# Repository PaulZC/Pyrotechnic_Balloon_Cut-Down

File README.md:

# Pyrotechnic Balloon Cut-Down Device

A lightweight wireless cut-down device for use on high altitude balloons.

Designed to be triggered by the [Iridium Beacon Radio Board](https://github.com/PaulZC/Iridium_Beacon_Radio_Board) and equipped with an
[LPRS eRIC4 or eRIC9 integrated radio module](http://www.lprs.co.uk/products/easyradio-ism-modules/eric-soc-rf-modules.html),
the cut-down will be triggered when the eRIC receives its own (unique) serial number on the chosen channel. The number of cut-downs that could be
triggered by a single Iridium Beacon is essentially unlimited.

See [How do I configure the altitude limit](https://github.com/PaulZC/Pyrotechnic_Balloon_Cut-Down/blob/master/LEARN.md#how-do-i-configure-the-altitude-limit)
for details on how to set the altitude limit using the I/O pins or via radio.

The cutter has been designed to reliably sever size 4N (2.4mm) braided nylon cord.

The cut-down device could also be used to control:
- a nichrome hot wire cord cutter
- a strobe or audible alarm
- any other device which can operate from 3.3V to 4.8V (depending on the battery voltage)

See [LEARN.md](https://github.com/PaulZC/Pyrotechnic_Balloon_Cut-Down/blob/master/LEARN.md) for further details.

See [ASSEMBLY.md](https://github.com/PaulZC/Pyrotechnic_Balloon_Cut-Down/blob/master/ASSEMBLY.md) for details on how to assemble and configure the PCB.

See [CUTTER.md](https://github.com/PaulZC/Pyrotechnic_Balloon_Cut-Down/blob/master/CUTTER.md) for details on how to assemble the mechanical parts.

See [Pyro_Cut-Down_V2.pdf](https://github.com/PaulZC/Pyrotechnic_Balloon_Cut-Down/blob/master/Pyro_Cut-Down_V2.pdf) for the schematic,
layout and Bill Of Materials.

The [Eagle](https://github.com/PaulZC/Pyrotechnic_Balloon_Cut-Down/tree/master/Eagle) directory contains the schematic and pcb design files.

The [eRIC](https://github.com/PaulZC/Pyrotechnic_Balloon_Cut-Down/tree/master/eRIC) directory contains the code for the eRIC integrated controller.

The [Drawings](https://github.com/PaulZC/Pyrotechnic_Balloon_Cut-Down/tree/master/Drawings) directory contains the drawings for the mechanical parts.

### Disclaimer

As this project involves the use of a very small quantity of smokeless gunpowder, the information contained herein should only be used by responsible adults
in full compliance with local laws and regulations regarding the purchase, transport, storage and use of smokeless powder. Follow the manufacturer's
instructions and safety information at all times. Appropriate Personal Protective Equipment must be used when handling gunpowder. Keep all parts of this
project out of the reach of children. Proceed entirely at your own risk.

The information contained herein is provided in good faith and is believed by the author to be both accurate and safe, but in no event shall the
author be liable for any injuries or damages resulting from the use of this information howsoever caused.

### Citation

If you have found this project useful and if you are able to, please cite the paper:

P. Clark et al, An open source toolkit for the tracking, termination and recovery of high altitude balloon flights and payloads, 2019 JINST 14 P04003
[DOI:10.1088/1748-0221/14/04/P04003](https://doi.org/10.1088/1748-0221/14/04/P04003)

The Accepted Manuscript is available on arXiv: http://arxiv.org/abs/1904.04321

### License

This project is distributed under a Creative Commons Attribution + Share-alike (BY-SA) licence.
Please refer to section 5 of the licence for the "Disclaimer of Warranties and Limitation of Liability".

Enjoy!

**_Paul_**

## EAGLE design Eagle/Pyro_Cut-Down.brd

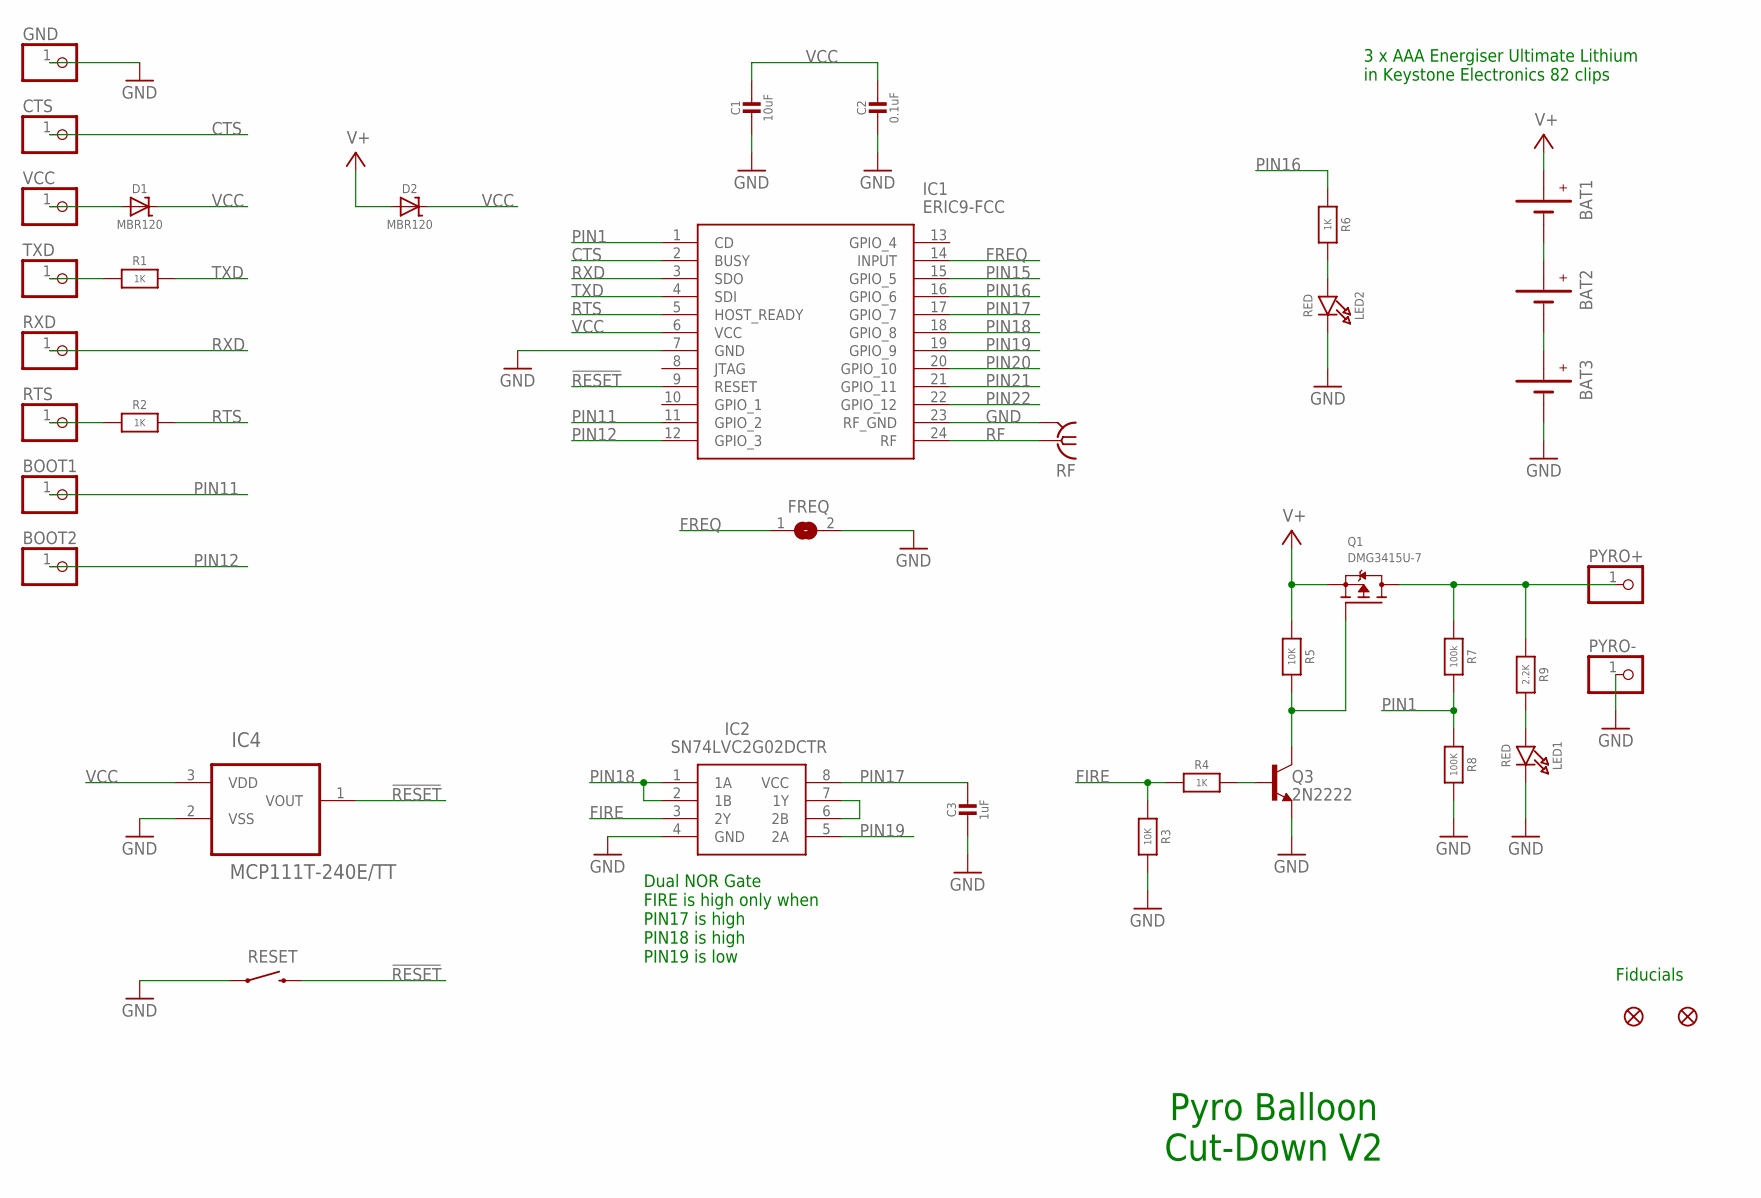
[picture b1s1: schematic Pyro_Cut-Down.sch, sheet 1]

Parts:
BAT1, BAT2, BAT3: BATTERYKEYSTONE82; BATTERY-AAA-KEYSTONE82
BOOT1, BOOT2: PINHD-1X1; 1X01
C1: 10uF; 0805-NO
C2: 0.1uF; 0603-NO
C3: 1uF; 0603-NO
CTS: PINHD-1X1; 1X01
D1, D2: MBR120; SOD-123
FD1, FD2: FIDUCIAL1X2; FIDUCIAL-1X2
FREQ: SOLDERJUMPER; SOLDERJUMPER_ARROW_NOPASTE
GND: PINHD-1X1; 1X01
IC1: ERIC9-FCC; ERIC4
IC2: SN74LVC2G02DCTR; SOP65P400X130-8N
IC4: MCP111T-240E/TT; SOT95P237X112-3N; MPN MCP111T-240E/TT
LED1, LED2: RED; CHIPLED_0805_NOOUTLINE
PYRO+: PINHD-1X1; 1X01
PYRO-: PINHD-1X1; 1X01
Q1: DMG3415U-7; SOT23-WIDE
Q3: 2N2222; SOT23-BEC
R1, R2, R4, R6: 1K; 0603-NO
R3, R5: 10K; 0603-NO
R7: 100k; 0603-NO
R8: 100K; 0603-NO
R9: 2.2K; 0603-NO
RESET: SWITCH-MOMENTARY-2PTH; TACTILE-PTH
RF: SMA-142-0711-821/826; J502-ND-142-0711-821/826
RTS: PINHD-1X1; 1X01
RXD: PINHD-1X1; 1X01
TXD: PINHD-1X1; 1X01
VCC: PINHD-1X1; 1X01

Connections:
!RESET: IC1.9 (RESET), IC4.1 (VOUT), RESET.3 (2); also elsewhere on the board
CTS: CTS.1, IC1.2 (BUSY)
FIRE: IC2.3 (2Y), R3.1, R4.1
FREQ: FREQ.1, IC1.14 (INPUT)
GND: BAT3.GND@1 (-), BAT3.GND@2 (-), C1.2, C2.2, C3.2, FREQ.2, GND.1, IC1.7 (GND), IC1.23 (RF_GND), IC2.4 (GND), IC4.2 (VSS), LED1.C, LED2.C, PYRO-.1, Q3.E, R3.2, R8.2, RESET.1, RF.G@1 (2), RF.G@2 (2), RF.G@3 (2), RF.G@4 (2); also elsewhere on the board
unnamed: BAT2.GND@1 (-), BAT2.GND@2 (-), BAT3.PWR@1 (+), BAT3.PWR@2 (+)
unnamed: LED2.A, R6.2
unnamed: BAT1.GND@1 (-), BAT1.GND@2 (-), BAT2.PWR@1 (+), BAT2.PWR@2 (+)
unnamed: LED1.A, R9.2
unnamed: R1.1, TXD.1
unnamed: IC2.6 (2B), IC2.7 (1Y)
unnamed: R2.1, RTS.1
unnamed: D1.A, VCC.1
unnamed: Q1.1 (G), Q3.C, R5.2
unnamed: Q3.B, R4.2
PIN1: IC1.1 (CD), R7.2, R8.1
PIN11: BOOT1.1, IC1.11 (GPIO_2)
PIN12: BOOT2.1, IC1.12 (GPIO_3)
PIN15: IC1.15 (GPIO_5); also elsewhere on the board
PIN16: IC1.16 (GPIO_6), R6.1
PIN17: C3.1, IC1.17 (GPIO_7), IC2.8 (VCC)
PIN18: IC1.18 (GPIO_8), IC2.1 (1A), IC2.2 (1B)
PIN19: IC1.19 (GPIO_9), IC2.5 (2A)
PIN20: IC1.20 (GPIO_10); also elsewhere on the board
PIN21: IC1.21 (GPIO_11); also elsewhere on the board
PIN22: IC1.22 (GPIO_12)
PYRO: PYRO+.1, Q1.3 (D), R7.1, R9.1
RF: IC1.24 (RF), RF.1
RTS: IC1.5 (HOST_READY), R2.2
RXD: IC1.3 (SDO), RXD.1
TXD: IC1.4 (SDI), R1.2
V+: BAT1.PWR@1 (+), BAT1.PWR@2 (+), D2.A, Q1.2 (S), R5.1
VCC: C1.1, C2.1, D1.C, D2.C, IC1.6 (VCC), IC4.3 (VDD); also elsewhere on the board

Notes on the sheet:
3 x AAA Energiser Ultimate Lithium in Keystone Electronics 82 clips
Pyro Balloon Cut-Down V2
Fiducials
Dual NOR Gate FIRE is high only when PIN17 is high PIN18 is high PIN19 is low

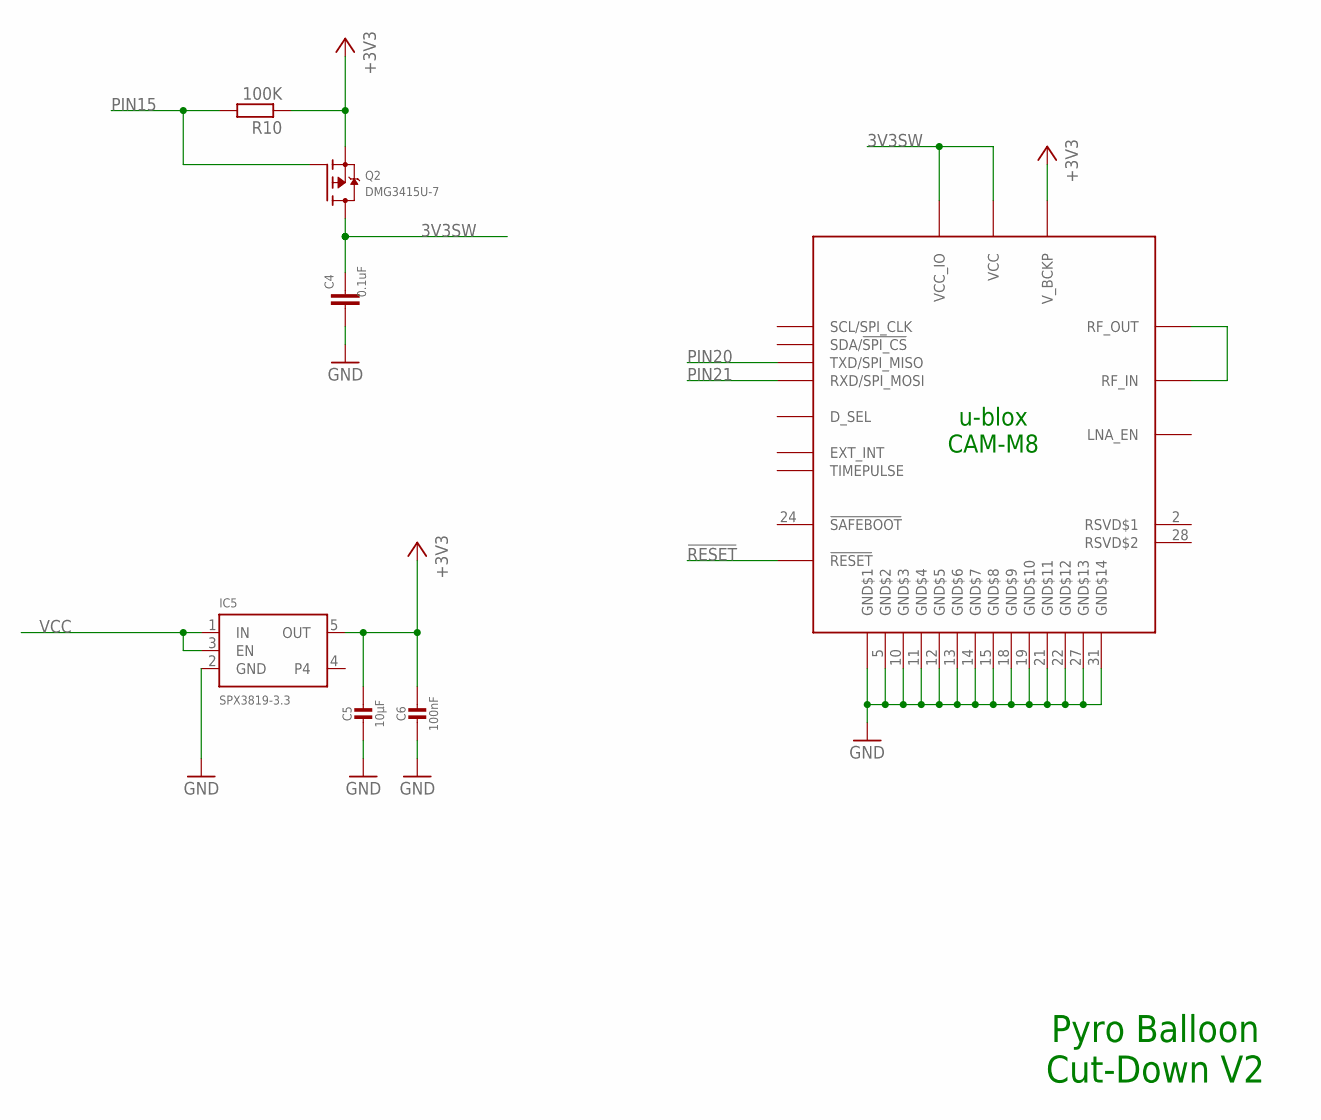
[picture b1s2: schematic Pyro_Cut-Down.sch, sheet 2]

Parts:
C4: 0.1uF; C0603
C5: 10µF; 0805-NO
C6: 100nF; 0603-NO
IC3: CAM-M8
IC5: SPX3819-3.3; SOT23-5
Q2: DMG3415U-7; SOT23-WIDE
R10: 100K; R0603

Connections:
3V3SW: C4.1, IC3.1 (VCC_IO), IC3.9 (VCC), Q2.3 (D)
!RESET: IC3.23 (!RESET); also elsewhere on the board
+3V3: C5.1, C6.1, IC3.8 (V_BCKP), IC5.5 (OUT), Q2.2 (S), R10.1
GND: C4.2, C5.2, C6.2, IC3.4 (GND$1), IC3.5 (GND$2), IC3.10 (GND$3), IC3.11 (GND$4), IC3.12 (GND$5), IC3.13 (GND$6), IC3.14 (GND$7), IC3.15 (GND$8), IC3.18 (GND$9), IC3.19 (GND$10), IC3.21 (GND$11), IC3.22 (GND$12), IC3.27 (GND$13), IC3.31 (GND$14), IC5.2 (GND); also elsewhere on the board
unnamed: IC3.16 (RF_OUT), IC3.17 (RF_IN)
PIN15: Q2.1 (G), R10.2; also elsewhere on the board
PIN20: IC3.25 (TXD/SPI_MISO); also elsewhere on the board
PIN21: IC3.26 (RXD/SPI_MOSI); also elsewhere on the board
VCC: IC5.1 (IN), IC5.3 (EN); also elsewhere on the board

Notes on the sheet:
u-blox CAM-M8
Pyro Balloon Cut-Down V2

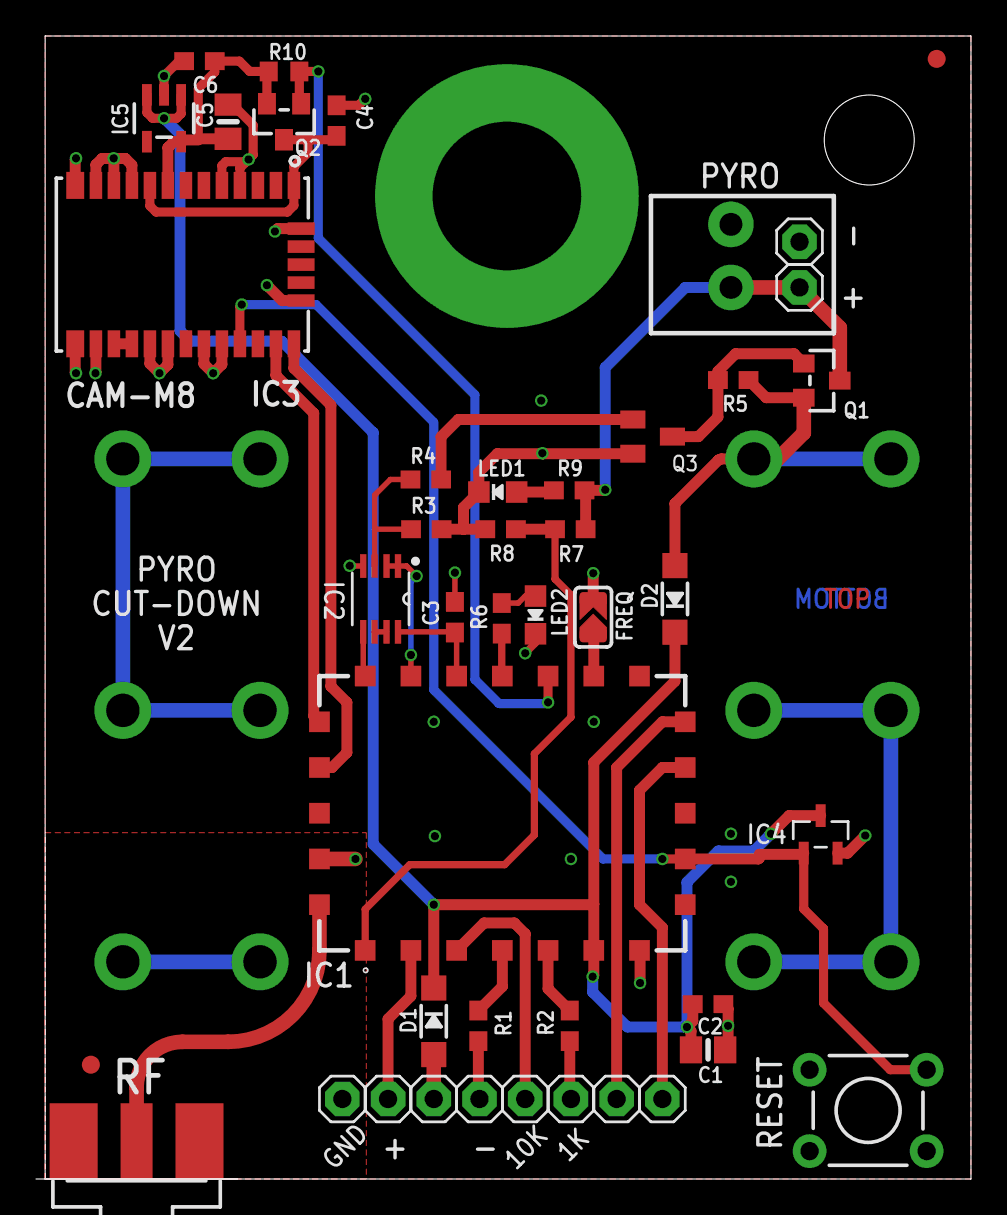
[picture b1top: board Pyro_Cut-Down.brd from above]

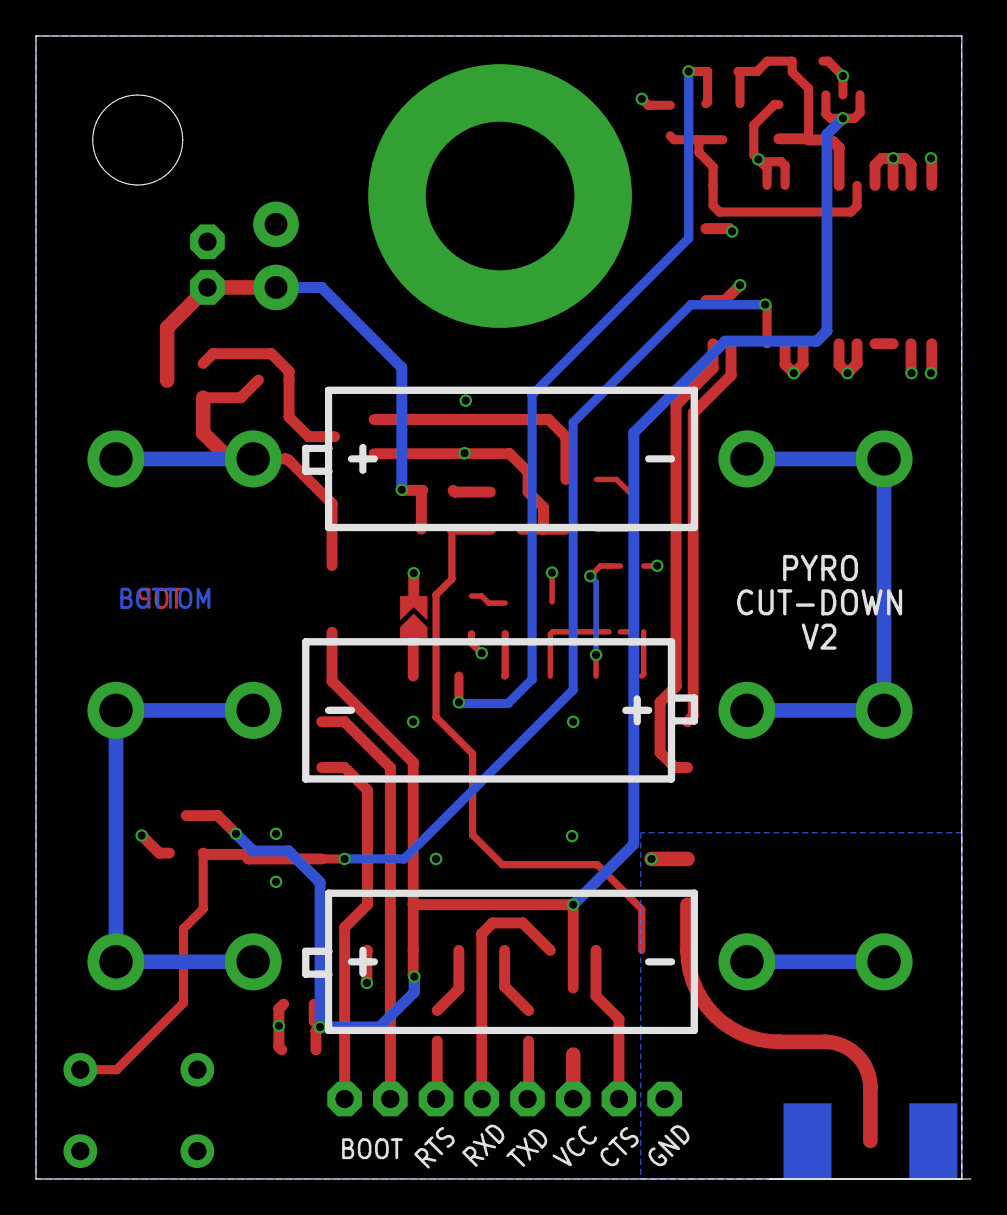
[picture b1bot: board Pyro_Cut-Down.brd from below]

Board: 2 copper layers, 51.9 x 63.5 mm, 46 parts (3 on the bottom side), 35 nets.

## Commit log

2018-09-24 First release
2018-09-24 Minor updates
2018-09-26 Updated the .brd images
2018-09-29 Updated LEARN.md
2018-10-12 Updated the eRIC code
2018-12-20 Major update for V2
    Major update for V2 of the PCB. Now includes a u-blox CAM-M8Q to provide accurate altitude data. Trigger-at-altitude is now possible.
2018-12-20 Minor corrections
2018-12-20 More minor corrections
2019-04-10 Added the citation

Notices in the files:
parts and their libraries:
microbuilder: This work is placed in the public domain, and may be freely used for commercial and non-commercial work with the following conditions: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
SparkFun-Electromechanical: Licensing: Creative Commons ShareAlike 4.0 International - https://creativecommons.org/licenses/by-sa/4.0
